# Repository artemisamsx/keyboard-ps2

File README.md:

# Artemisa MSX - PS/2 Keyboard Adapter

This repository contains the KiCad project files for the PS/2 Keyboard adapter.

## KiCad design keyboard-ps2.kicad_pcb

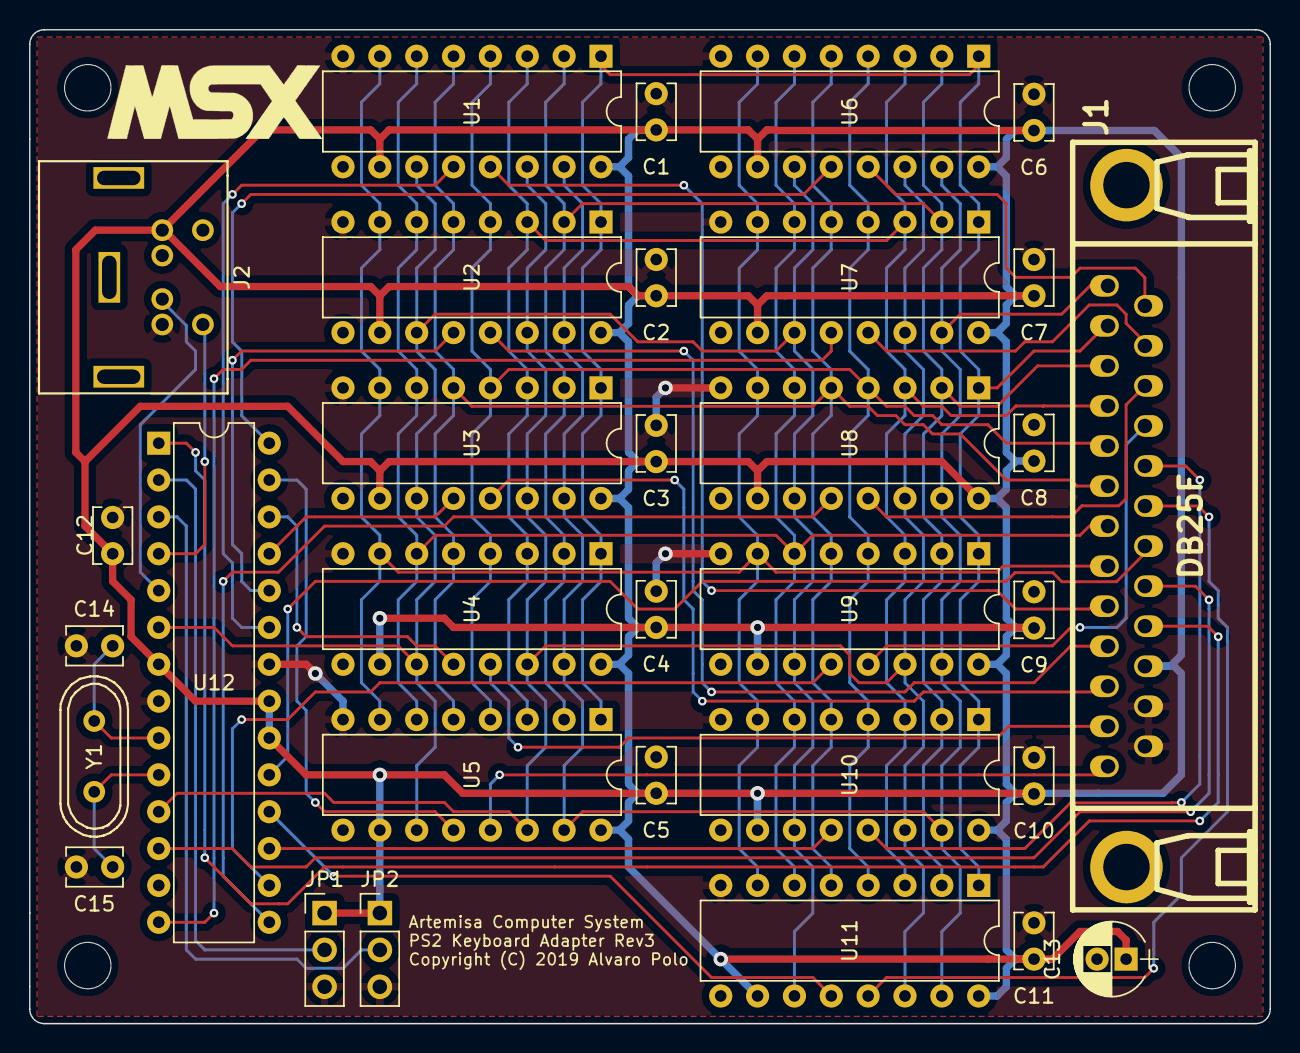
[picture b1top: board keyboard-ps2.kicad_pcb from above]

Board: 2 copper layers, 85.5 x 68.5 mm, 32 parts (0 on the bottom side), 43 nets.

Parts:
C1, C2, C3, C4, C5, C6, C7, C8, C9, C10, C11, C12: 100nF; Disc_capacitor
C13: 10uF; Radial_capacitor
C14, C15: 33pF; Disc_capacitor
J1: DB25F
J2: PS2_CONN; PS2_conn
JP1, JP2: Jumper
U1, U2, U3, U4, U5, U6, U7, U8, U9, U10, U11: 74HC595; DIP-16_300
U12: ATMEGA328P; DIP-28_300
Y1: 16Mhz; Crystal

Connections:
/DS: U1.14, U2.14, U3.14, U4.14, U5.14, U6.14, U7.14, U8.14, U9.14, U10.14, U11.14, U12.11
/KBCOL0: J1.1, U1.15, U2.15, U3.15, U4.15, U5.15, U6.15, U7.15, U8.15, U9.15, U10.15, U11.15
/KBCOL1: J1.2, U1.1, U2.1, U3.1, U4.1, U5.1, U6.1, U7.1, U8.1, U9.1, U10.1, U11.1
/KBCOL2: J1.3, U1.2, U2.2, U3.2, U4.2, U5.2, U6.2, U7.2, U8.2, U9.2, U10.2, U11.2
/KBCOL3: J1.4, U1.3, U2.3, U3.3, U4.3, U5.3, U6.3, U7.3, U8.3, U9.3, U10.3, U11.3
/KBCOL4: J1.5, U1.4, U2.4, U3.4, U4.4, U5.4, U6.4, U7.4, U8.4, U9.4, U10.4, U11.4
/KBCOL5: J1.6, U1.5, U2.5, U3.5, U4.5, U5.5, U6.5, U7.5, U8.5, U9.5, U10.5, U11.5
/KBCOL6: J1.7, U1.6, U2.6, U3.6, U4.6, U5.6, U6.6, U7.6, U8.6, U9.6, U10.6, U11.6
/KBCOL7: J1.8, U1.7, U2.7, U3.7, U4.7, U5.7, U6.7, U7.7, U8.7, U9.7, U10.7, U11.7
/SHCP: U1.11, U2.11, U3.11, U4.11, U5.11, U6.11, U7.11, U8.11, U9.11, U10.11, U11.11, U12.6
/STCP0: U1.12, U12.23
/STCP1: U2.12, U12.24
/STCP2: U3.12, U12.25
/STCP3: U4.12, U12.26
/STCP4: U5.12, U12.27
/STCP5: U6.12, U12.28
/STCP6: U7.12, U12.14
/STCP7: U8.12, U12.15
/STCP8: U9.12, U12.16
/STCP9: U10.12, U12.17
/STCP10: U11.12, U12.18
/~CAPSLOCK: J1.20, U12.19
/~KANALOCK: J1.21, U12.12
/~RESET: J1.22, U12.1
/~RSL0: J1.9, U1.13
/~RSL1: J1.10, U2.13
/~RSL2: J1.11, U3.13
/~RSL3: J1.12, U4.13
/~RSL4: J1.13, U5.13
/~RSL5: J1.14, U6.13
/~RSL6: J1.15, U7.13
/~RSL7: J1.16, U8.13
/~RSL8: J1.17, U9.13
/~RSL9: J1.18, U10.13
/~RSL10: J1.19, U11.13
GND: C1.2, C2.2, C3.2, C4.2, C5.2, C6.2, C7.2, C8.2, C9.2, C10.2, C11.2, C12.2, C13.2, C14.2, C15.2, J1.24, J1.25, J2.3, JP1.3, JP2.3, U1.8, U2.8, U3.8, U4.8, U5.8, U6.8, U7.8, U8.8, U9.8, U10.8, U11.8, U12.8, U12.22
unnamed: C14.1, U12.9, Y1.1
unnamed: C15.1, U12.10, Y1.2
unnamed: J2.1, U12.5
unnamed: J2.5, U12.4
unnamed: JP1.2, U12.2
unnamed: JP2.2, U12.3
~: C1.1, C2.1, C3.1, C4.1, C5.1, C6.1, C7.1, C8.1, C9.1, C10.1, C11.1, C12.1, C13.1, J1.23, J2.4, JP1.1, JP2.1, U1.10, U1.16, U2.10, U2.16, U3.10, U3.16, U4.10, U4.16, U5.10, U5.16, U6.10, U6.16, U7.10, U7.16, U8.10, U8.16, U9.10, U9.16, U10.10, U10.16, U11.10, U11.16, U12.7, U12.20, U12.21

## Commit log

2019-04-15 Add schematic for keyboard PS2 adapter project
2019-04-15 Add PCB design for PS2 Keyboard Adapter
2019-04-17 Add pins for optional pin header in DB25 footprints
    We might want to use an internal connection to a pin header of 100millis instead of the DB25 connector. So we have included additional pins to sold such pin header instead of DB25 header.
2019-04-17 Add KANALOCK signals to keyboard connectors
    Still not used from the motherboard (wired to 5v).
2019-04-21 Fix DB25 connector of keyboard PS2 PCB
    So it stands out from the board.
2019-04-29 Plot PS2 Keyboard Adapter PCB
2019-05-21 Shorten the PCB and the DB25 connector in PS2 Adapter
2019-07-16 Increse width of power tracks in PS2 Keyboard Adapter
2019-09-02 [ps2-adapter] Add 2 jumpers for KB layout selection
2019-09-02 [ps2-adapter] Add changelog file
2019-09-04 [ps2-adapter] Fix capacitor values for clock circuit
2019-09-05 [ps2-adapter] Set board settings to match JCLPCB design rules
2019-09-05 Update changelogs and revision numbers of all PCBs
2019-09-05 Fix changelog files to reflect unreleased changes
2019-09-10 [motherboard] Update changelog
2019-09-10 [motherboard] Fix wrong annular ring size of cartridge slot connectors
2019-09-12 [ps2-keyboard] Make the PCB corners rounded
2019-09-12 Release artemisa-mk1_rev3
2020-03-10 Reorganize command processing
2021-03-23 Add README and LICENSE files
2021-03-23 Add kicadlibs as submodule

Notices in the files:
keyboard-ps2.kicad_pcb:
Copyright (C) 2019 Alvaro Polo
